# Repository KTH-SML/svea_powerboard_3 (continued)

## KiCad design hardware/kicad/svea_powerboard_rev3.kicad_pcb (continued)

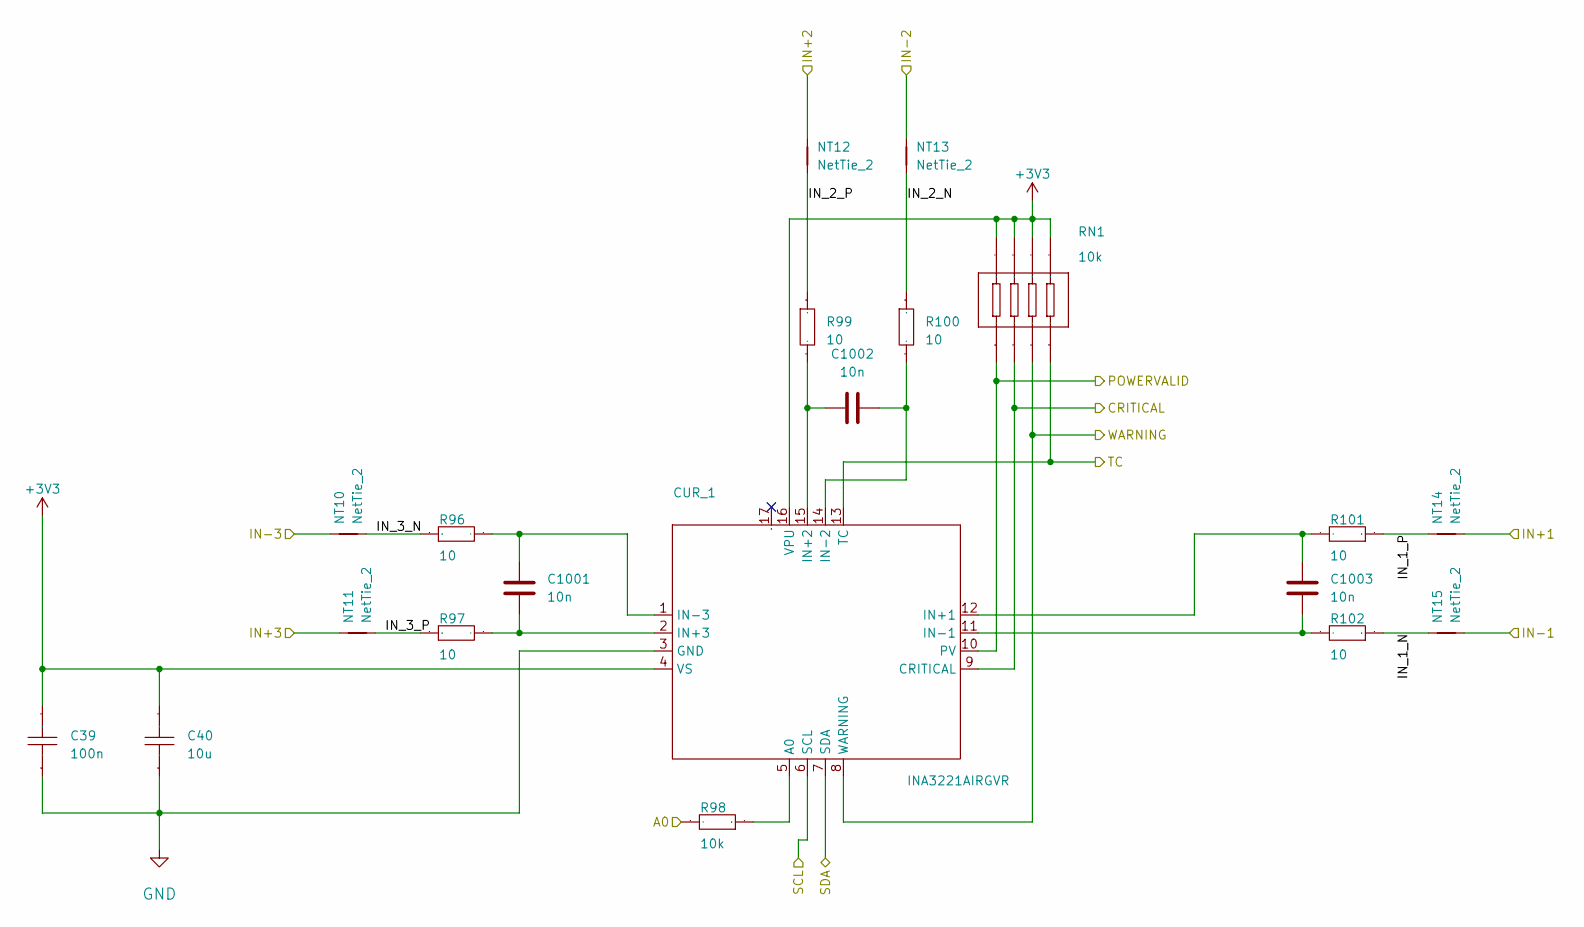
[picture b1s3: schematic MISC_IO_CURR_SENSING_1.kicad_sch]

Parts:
C39: 100n; C_0603_1608Metric; Manufacturer Part CC0603KRX7R9BB104; LCSC Part Name 100nF ±10% 50V
C40: 10u; C_0805_2012Metric; Manufacturer Part GRM21BR61H106KE43L; LCSC Part Name 10uF ±10% 50V
C1001, C1002, C1003: 10n; C_0402_1005Metric; LCSC C15195
CUR_1: INA3221AIRGVR; Texas_RGV0016A_VQFN-16-1EP_4x4mm_P0.65mm_EP2.1x2.1mm; Manufacturer Part INA3221AIRGVR; LCSC Part Name INA3221AIRGVR
NT10, NT11, NT12, NT13, NT14, NT15: NetTie_2; NetTie-2_SMD_Pad0.2mm
R96, R97, R99, R100, R101, R102: 10; R_0402_1005Metric; Manufacturer Part RC0402FR-0710RL; LCSC Part Name 厚膜电阻 10Ω ±1% 62.5mW
R98: 10k; R_0402_1005Metric; Manufacturer Part 0402WGF1002TCE; LCSC Part Name 10kΩ ±1% 62.5mW 厚膜电阻
RN1: 10k; R_Array_Convex_4x0603; Manufacturer Part RTA03-4D103JTP; LCSC Part Name 10kΩ ±5%

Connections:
+3V3: C39.2, C40.2, CUR_1.4 (VS), CUR_1.16 (VPU), RN1.5, RN1.6, RN1.7, RN1.8; also elsewhere on the board
+12V: NT11.2, NT12.2, NT14.1; also elsewhere on the board
/Battery System/CUR1/IN-1: NT15.1; also elsewhere on the board
/Battery System/CUR1/IN-2: NT13.2; also elsewhere on the board
/Battery System/CUR1/IN-3: NT10.2; also elsewhere on the board
/Battery System/CUR1/IN_1_N: NT15.2, R102.1
/Battery System/CUR1/IN_1_P: NT14.2, R101.1
/Battery System/CUR1/IN_2_N: NT13.1, R100.1
/Battery System/CUR1/IN_2_P: NT12.1, R99.1
/Battery System/CUR1/IN_3_N: NT10.1, R96.1
/Battery System/CUR1/IN_3_P: NT11.1, R97.1
Current/INA3221-CUR1/CRITICAL: CUR_1.9 (CRITICAL), RN1.2; also elsewhere on the board
Current/INA3221-CUR1/POWERVALID: CUR_1.10 (PV), RN1.1; also elsewhere on the board
Current/INA3221-CUR1/TC: CUR_1.13 (TC), RN1.4; also elsewhere on the board
Current/INA3221-CUR1/WARNING: CUR_1.8 (WARNING), RN1.3; also elsewhere on the board
GND: C39.1, C40.1, CUR_1.3 (GND), R98.2; also elsewhere on the board
unnamed: CUR_1.5 (A0), R98.1
unnamed: C1003.2, CUR_1.12 (IN+1), R101.2
unnamed: C1002.1, CUR_1.15 (IN+2), R99.2
unnamed: C1001.2, CUR_1.2 (IN+3), R97.2
unnamed: C1003.1, CUR_1.11 (IN-1), R102.2
unnamed: C1002.2, CUR_1.14 (IN-2), R100.2
unnamed: C1001.1, CUR_1.1 (IN-3), R96.2
SCL_SLOW: CUR_1.6 (SCL); also elsewhere on the board
SDA_SLOW: CUR_1.7 (SDA); also elsewhere on the board

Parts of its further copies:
C102: 100n; C_0603_1608Metric; Manufacturer Part CC0603KRX7R9BB104; LCSC Part Name 100nF ±10% 50V
C103: 10u; C_0805_2012Metric; Manufacturer Part GRM21BR61H106KE43L; LCSC Part Name 10uF ±10% 50V
C2801, C2802, C2803: 10n; C_0402_1005Metric; LCSC C15195
CUR_2: INA3221AIRGVR; Texas_RGV0016A_VQFN-16-1EP_4x4mm_P0.65mm_EP2.1x2.1mm; Manufacturer Part INA3221AIRGVR; LCSC Part Name INA3221AIRGVR
NT20, NT21, NT22, NT23, NT24, NT25: NetTie_2; NetTie-2_SMD_Pad0.2mm
R160, R161, R163, R164, R165, R166: 10; R_0402_1005Metric; Manufacturer Part RC0402FR-0710RL; LCSC Part Name 厚膜电阻 10Ω ±1% 62.5mW
R162: 10k; R_0402_1005Metric; Manufacturer Part 0402WGF1002TCE; LCSC Part Name 10kΩ ±1% 62.5mW 厚膜电阻
RN2: 10k; R_Array_Convex_4x0603; Manufacturer Part RTA03-4D103JTP; LCSC Part Name 10kΩ ±5%

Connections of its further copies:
+3V3: C102.2, C103.2, CUR_2.4 (VS), CUR_2.16 (VPU), R162.2, RN2.5, RN2.6, RN2.7, RN2.8; also elsewhere on the board
+12V: NT20.2; also elsewhere on the board
/Battery System/CUR2/IN+3: NT21.2; also elsewhere on the board
/Battery System/CUR2/IN-1: NT25.1; also elsewhere on the board
/Battery System/CUR2/IN-2: NT23.2; also elsewhere on the board
/Battery System/CUR2/IN_1_N: NT25.2, R166.1
/Battery System/CUR2/IN_1_P: NT24.2, R165.1
/Battery System/CUR2/IN_2_N: NT23.1, R164.1
/Battery System/CUR2/IN_2_P: NT22.1, R163.1
/Battery System/CUR2/IN_3_N: NT20.1, R160.1
/Battery System/CUR2/IN_3_P: NT21.1, R161.1
Current/INA3221-CUR2/CRITICAL: CUR_2.9 (CRITICAL), RN2.2; also elsewhere on the board
Current/INA3221-CUR2/POWERVALID: CUR_2.10 (PV), RN2.1; also elsewhere on the board
Current/INA3221-CUR2/TC: CUR_2.13 (TC), RN2.4; also elsewhere on the board
Current/INA3221-CUR2/WARNING: CUR_2.8 (WARNING), RN2.3; also elsewhere on the board
GND: C102.1, C103.1, CUR_2.3 (GND); also elsewhere on the board
unnamed: CUR_2.5 (A0), R162.1
unnamed: C2803.2, CUR_2.12 (IN+1), R165.2
unnamed: C2802.1, CUR_2.15 (IN+2), R163.2
unnamed: C2801.2, CUR_2.2 (IN+3), R161.2
unnamed: C2803.1, CUR_2.11 (IN-1), R166.2
unnamed: C2802.2, CUR_2.14 (IN-2), R164.2
unnamed: C2801.1, CUR_2.1 (IN-3), R160.2
PACK+: NT22.2; also elsewhere on the board
SCL_SLOW: CUR_2.6 (SCL); also elsewhere on the board
SDA_SLOW: CUR_2.7 (SDA); also elsewhere on the board
VCC: NT24.1; also elsewhere on the board

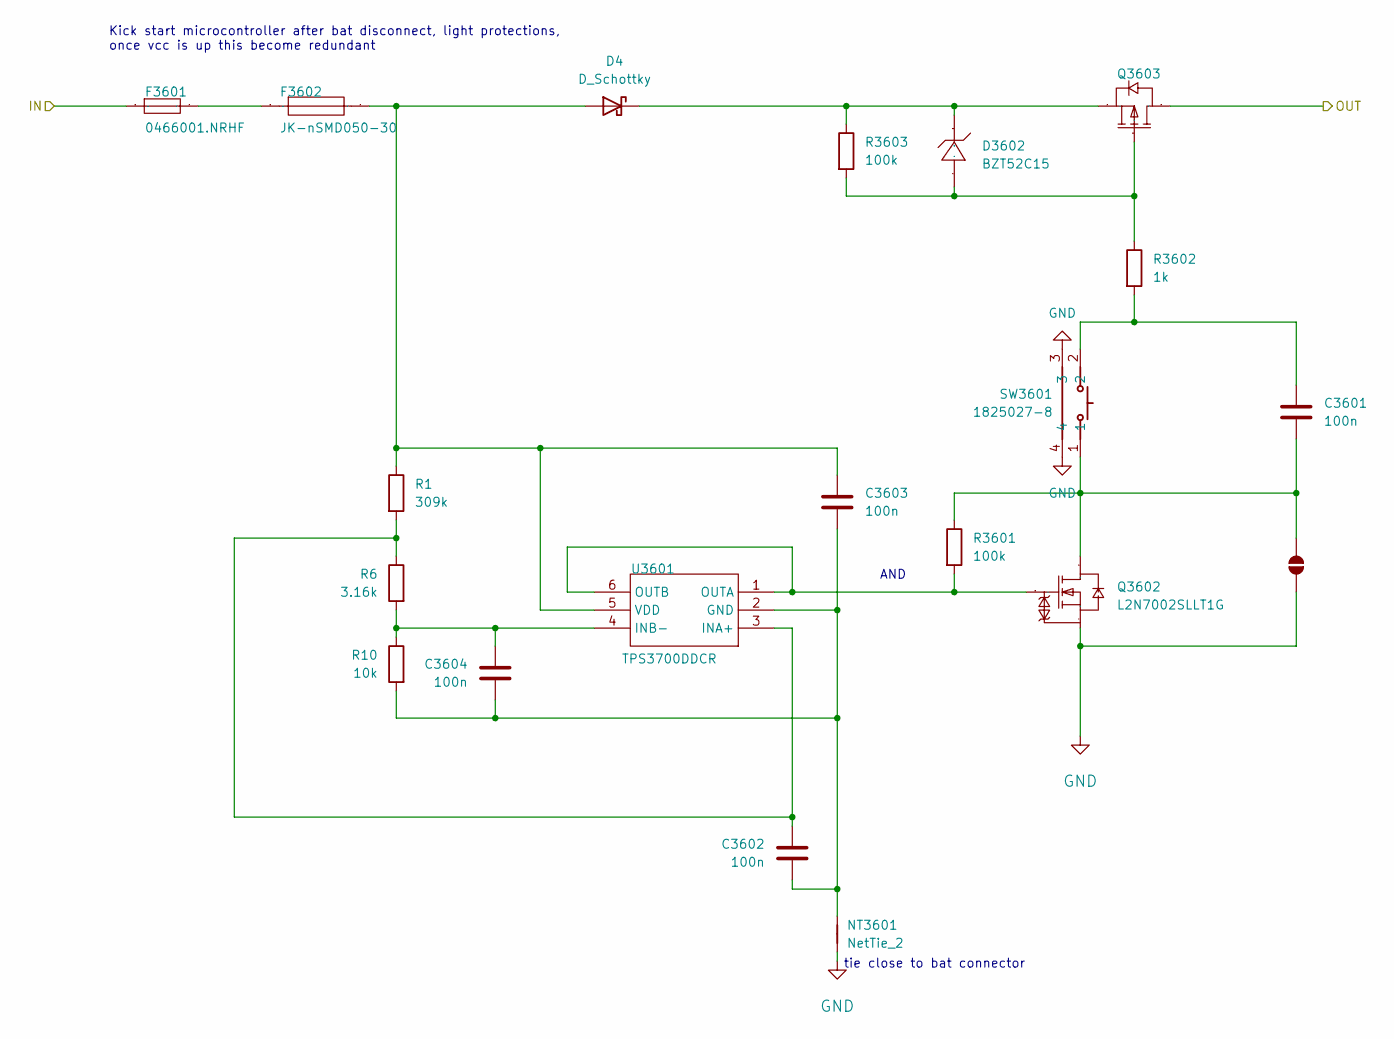
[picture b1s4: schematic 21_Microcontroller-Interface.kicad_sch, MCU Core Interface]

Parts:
C3601, C3602, C3603, C3604: 100n; C_0402_1005Metric; LCSC C307331
D4: D_Schottky; D_SOD-123F; LCSC C719833
D3602: BZT52C15; D_SOD-123; Manufacturer Part BZT52C15; LCSC Part Name BZT52C15
F3601: 0466001.NRHF; Fuse_1206_3216Metric; Manufacturer Part 0466001.NRHF; LCSC Part Name 63V贴片式保险丝
F3602: JK-nSMD050-30; Fuse_1206_3216Metric; Manufacturer Part JK-nSMD050-30; LCSC Part Name 30V 500mA 1206自恢复
JP3601: SolderJumper_2_Open; SolderJumper-2_P1.3mm_Open_TrianglePad1.0x1.5mm
NT3601: NetTie_2; NetTie-2_SMD_Pad0.2mm
Q3602: L2N7002SLLT1G; SOT-23; Manufacturer Part L2N7002SLLT1G; LCSC Part Name 1个N沟道 耐压:60V 电流:380mA
Q3603: SI2309A; SOT-23; Manufacturer Part SI2309A; LCSC Part Name 1个P沟道 耐压:60V 电流:1.25A
R1: 309k; R_0402_1005Metric
R6: 3.16k; R_0402_1005Metric
R10: 10k; R_0402_1005Metric
R3601, R3603: 100k; R_0402_1005Metric; LCSC C25741
R3602: 1k; R_0402_1005Metric; LCSC C11702
SW3601: 1825027-8; Manufacturer Part 1825027-8; LCSC C266196
U3601: TPS3700DDCR; SOT-23-6; Manufacturer Part TPS3700DDCR; LCSC Part Name 用于过压和欠压检测的窗口比较器

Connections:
/Battery System/Battery BMS Interface/BQ-BAT: F3601.1; also elsewhere on the board
/Battery System/danger_rail: Q3603.3 (D); also elsewhere on the board
GND: JP3601.1 (A), NT3601.1, Q3602.2 (S), SW3601.3, SW3601.4; also elsewhere on the board
unnamed: C3601.1, R3602.2, SW3601.2
unnamed: C3603.1, D4.2 (A), F3602.2, R1.1, U3601.5 (VDD)
unnamed: D3602.2 (A), Q3603.1 (G), R3602.1, R3603.2
unnamed: D4.1 (K), D3602.1 (K), Q3603.2 (S), R3603.1
unnamed: F3601.2, F3602.1
unnamed: C3601.2, JP3601.2 (B), Q3602.3 (D), R3601.1, SW3601.1
unnamed: Q3602.1 (G), R3601.2, U3601.1 (OUTA), U3601.6 (OUTB)
unnamed: C3602.2, C3603.2, C3604.2, NT3601.2, R10.2, U3601.2 (GND)
unnamed: C3602.1, R1.2, R6.1, U3601.3 (INA+)
unnamed: C3604.1, R6.2, R10.1, U3601.4 (INB-)

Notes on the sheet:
Kick start microcontroller after bat disconnect, light protections, once vcc is up this become redundant
AND
tie close to bat connector

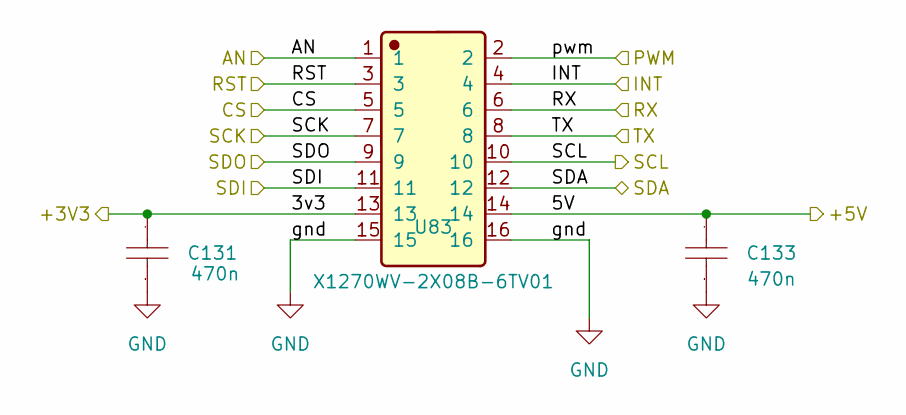
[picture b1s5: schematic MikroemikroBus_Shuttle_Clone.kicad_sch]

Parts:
C131, C133: 470n; C_0603_1608Metric; Manufacturer Part 0603B474K500NT; LCSC Part Name 470nF ±10% 50V
U83: X1270WV-2X08B-6TV01; Manufacturer Part X1270WV-2x08B-9TV01; LCSC C5147219

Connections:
+3V3: C131.2, U83.13; also elsewhere on the board
+5V: C133.2, U83.14; also elsewhere on the board
/Battery System/Mikroe mikroBus Shuttle Clone VITAL/CS: U83.5
/Battery System/Mikroe mikroBus Shuttle Clone VITAL/RST: U83.3
/Battery System/Mikroe mikroBus Shuttle Clone VITAL/SCK: U83.7
/Battery System/Mikroe mikroBus Shuttle Clone VITAL/SDI: U83.11
/Battery System/Mikroe mikroBus Shuttle Clone VITAL/SDO: U83.9
/Battery System/Mikroe mikroBus Shuttle Clone VITAL/TX: U83.8
Button/LOW: U83.1; also elsewhere on the board
GND: C131.1, C133.1, U83.15, U83.16; also elsewhere on the board
IO-Expander/Primary/INT: U83.4; also elsewhere on the board
LED/WS2815/DATA: U83.2; also elsewhere on the board
SBUS_RECEIVER: U83.6; also elsewhere on the board
SCL_SLOW: U83.10; also elsewhere on the board
SDA_SLOW: U83.12; also elsewhere on the board

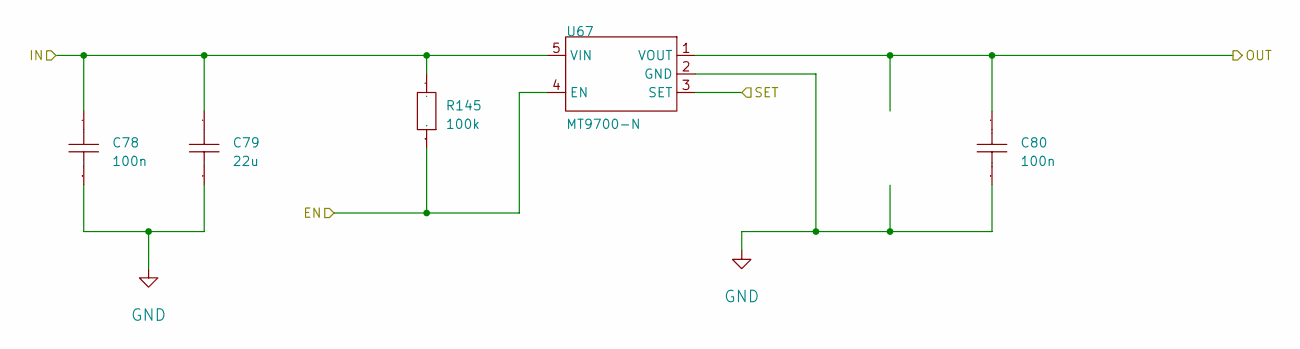
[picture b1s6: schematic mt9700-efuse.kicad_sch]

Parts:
C78, C80: 100n; C_0603_1608Metric; Manufacturer Part CC0603KRX7R9BB104; LCSC Part Name 100nF ±10% 50V
C79: 22u; C_0603_1608Metric; Manufacturer Part CL10A226MP8NUNE; LCSC Part Name 22uF ±20% 10V
R145: 100k; R_0603_1608Metric; Manufacturer Part FRC0603J104 TS; LCSC Part Name 100kΩ ±5% 100mW 厚膜电阻
U67: MT9700-N; SOT-23-5_L2.9-W1.6-P0.95-LS2.9-BL; Manufacturer Part MT9700-N; LCSC Part Name 可调快速响应、限流型电源分配开关

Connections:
+3V3: C78.2, C79.2, R145.2, U67.5 (VIN); also elsewhere on the board
/Battery System/ServoConnectors/3v3: C80.2, U67.1 (VOUT); also elsewhere on the board
/Battery System/mt9700-efuse/SET: U67.3 (SET); also elsewhere on the board
GND: C78.1, C79.1, C80.1, U67.2 (GND); also elsewhere on the board
Receiver/EN: R145.1, U67.4 (EN); also elsewhere on the board

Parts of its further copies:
C107, C109: 100n; C_0603_1608Metric; Manufacturer Part CC0603KRX7R9BB104; LCSC Part Name 100nF ±10% 50V
C108: 22u; C_0603_1608Metric; Manufacturer Part CL10A226MP8NUNE; LCSC Part Name 22uF ±20% 10V
R168: 100k; R_0603_1608Metric; Manufacturer Part FRC0603J104 TS; LCSC Part Name 100kΩ ±5% 100mW 厚膜电阻
U76: MT9700-N; SOT-23-5_L2.9-W1.6-P0.95-LS2.9-BL; Manufacturer Part MT9700-N; LCSC Part Name 可调快速响应、限流型电源分配开关

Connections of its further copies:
+LCL_5V: C109.2, U76.1 (VOUT); also elsewhere on the board
/Battery System/5v rail/5V buck rail: C107.2, C108.2, R168.2, U76.5 (VIN); also elsewhere on the board
/Battery System/mt9700-efuse1/EN: R168.1, U76.4 (EN)
/Battery System/mt9700-efuse1/SET: U76.3 (SET); also elsewhere on the board
GND: C107.1, C108.1, C109.1, U76.2 (GND); also elsewhere on the board

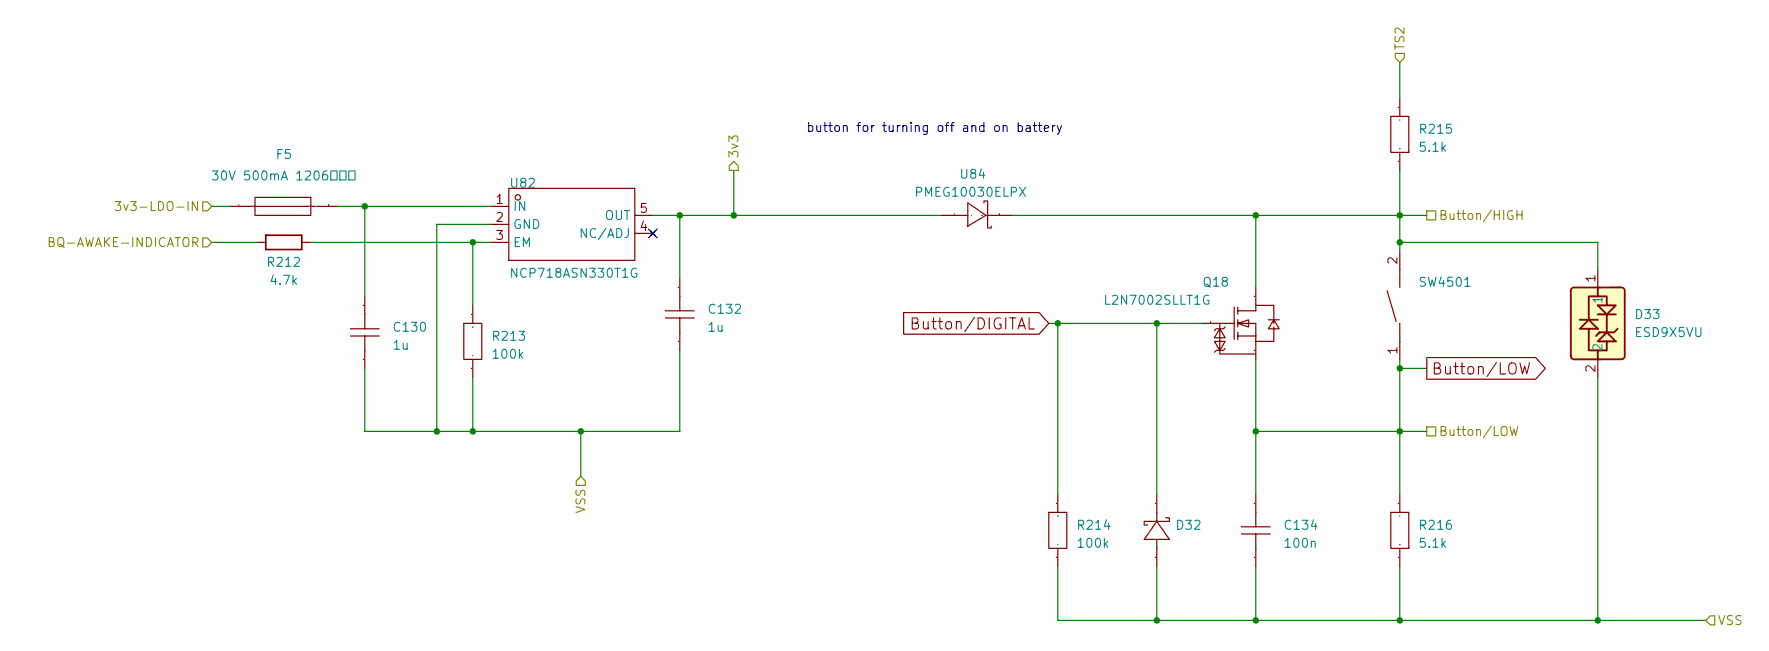
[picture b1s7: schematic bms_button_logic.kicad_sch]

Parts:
C130, C132: 1u; C_0603_1608Metric; Manufacturer Part CL10A105KB8NNNC; LCSC Part Name 1uF ±10% 50V
C134: 100n; C_0603_1608Metric; Manufacturer Part CC0603KRX7R9BB104; LCSC Part Name 100nF ±10% 50V
D32: UCLAMP3301P; DFN1006-2L-RD; Manufacturer Part UCLAMP3301P; LCSC Part Name 单向TVS 3.3V截止 峰值浪涌电流：4A@8/20us
D33: ESD9X5VU; Manufacturer Part ESD9X5VU; LCSC C2875160
F5: JK-nSMD050-30; Fuse_1206_3216Metric; Manufacturer Part JK-nSMD050-30; LCSC Part Name 30V 500mA 1206自恢复
Q18: L2N7002SLLT1G; SOT-23; Manufacturer Part L2N7002SLLT1G; LCSC Part Name 1个N沟道 耐压:60V 电流:380mA
R212: 4.7k; R_0603_1608Metric; LCSC C23162
R213, R214: 100k; R_0603_1608Metric; Manufacturer Part FRC0603J104 TS; LCSC Part Name 100kΩ ±5% 100mW 厚膜电阻
R215, R216: 5.1k; R_0603_1608Metric; Manufacturer Part FRC0603F5101TS; LCSC Part Name 5.1kΩ ±1% 100mW 厚膜电阻
SW4501: TS-1088-AR02016; SW-SMD_L3.9-W3.0-P4.45; Manufacturer Part TS-1088-AR02016; LCSC Part Name 4*3*2mm 立贴 轻触开关
U82: NCP718ASN330T1G; TSOT-23-5; Manufacturer Part NCP718ASN330T1G; LCSC Part Name NCP718ASN330T1G
U84: PMEG10030ELPX; D_SOD-128; Manufacturer Part PMEG10030ELPX; LCSC Part Name 电压:100V 电流:3A

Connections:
/Battery System/Battery BMS Interface/ALERT_PULLUP: C132.2, U82.5 (OUT), U84.2 (A); also elsewhere on the board
/Battery System/Battery BMS Interface/BQ-BAT: F5.2; also elsewhere on the board
/Battery System/Battery BMS Interface/REG18: R212.2; also elsewhere on the board
/Battery System/Battery BMS Interface/TS2: R215.2; also elsewhere on the board
/Battery System/Battery BMS Interface/VSS: C130.1, C132.1, C134.1, D32.2 (A), D33.2, R213.2, R214.2, R216.1, U82.2 (GND); also elsewhere on the board
/Battery System/bms_button_logic/Button/HIGH: D33.1, Q18.3 (D), R215.1, SW4501.2, U84.1 (K)
Button/DIGITAL: D32.1 (K), Q18.1 (G), R214.1; also elsewhere on the board
Button/LOW: C134.2, Q18.2 (S), R216.2, SW4501.1; also elsewhere on the board
unnamed: R212.1, R213.1, U82.3 (EM)
unnamed: C130.2, F5.1, U82.1 (IN)

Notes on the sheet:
button for turning off and on battery

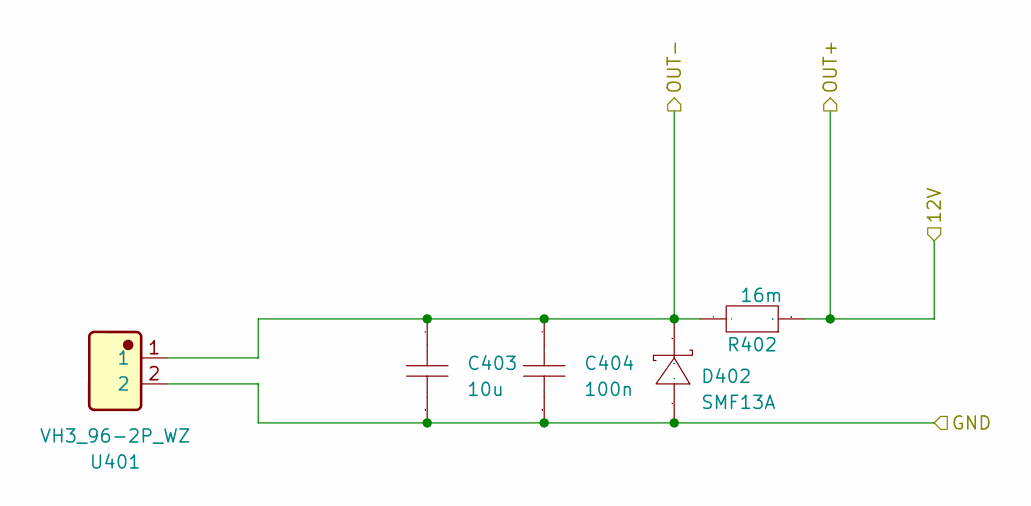
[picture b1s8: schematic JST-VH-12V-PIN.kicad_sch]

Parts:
C403: 10u; C_0805_2012Metric; Manufacturer Part GRM21BR61H106KE43L; LCSC Part Name 10uF ±10% 50V
C404: 100n; C_0603_1608Metric; Manufacturer Part CC0603KRX7R9BB104; LCSC Part Name 100nF ±10% 50V
D402: SMF13A; SOD-123FL_L2.8-W1.8-LS3.6-RD; Manufacturer Part SMF13A; LCSC Part Name SMF13A
R402: 16m; R_2512_6332Metric; Manufacturer Part LR123WF160MT4E; LCSC Part Name 16mΩ ±1% 3W
U401: VH3_96-2P_WZ; Manufacturer Part VH3.96-2P WZ; LCSC C5379879

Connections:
+12V: R402.1; also elsewhere on the board
/Battery System/CUR1/IN-3: C403.2, C404.2, D402.1 (K), R402.2, U401.1; also elsewhere on the board
GND: C403.1, C404.1, D402.2 (A), U401.2; also elsewhere on the board

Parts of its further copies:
C46, C501: 10u; C_0805_2012Metric; Manufacturer Part GRM21BR61H106KE43L; LCSC Part Name 10uF ±10% 50V
C47, C502: 100n; C_0603_1608Metric; Manufacturer Part CC0603KRX7R9BB104; LCSC Part Name 100nF ±10% 50V
D14, D501: SMF13A; SOD-123FL_L2.8-W1.8-LS3.6-RD; Manufacturer Part SMF13A; LCSC Part Name SMF13A
R104, R501: 16m; R_2512_6332Metric; Manufacturer Part LR123WF160MT4E; LCSC Part Name 16mΩ ±1% 3W
U42, U501: VH3_96-2P_WZ; Manufacturer Part VH3.96-2P WZ; LCSC C5379879

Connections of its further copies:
+12V: R104.1, R501.1; also elsewhere on the board
/Battery System/CUR1/IN-1: C501.2, C502.2, D501.1 (K), R501.2, U501.1; also elsewhere on the board
/Battery System/CUR1/IN-2: C46.2, C47.2, D14.1 (K), R104.2, U42.1; also elsewhere on the board
GND: C46.1, C47.1, C501.1, C502.1, D14.2 (A), D501.2 (A), U42.2, U501.2; also elsewhere on the board

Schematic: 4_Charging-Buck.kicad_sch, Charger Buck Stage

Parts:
C20, C21: 22u; C_1210_3225Metric; LCSC C778721
C23: 100n; C_0603_1608Metric; Manufacturer Part CC0603KRX7R9BB104; LCSC Part Name 100nF ±10% 50V
C32: RVT1H220M0605; Manufacturer Part RVT1H220M0605; LCSC C72505
C601: 10u; C_1206_3216Metric; LCSC C89632
C602: UWT1H221MNL1GS; Manufacturer Part UWT1H221MNL1GS; LCSC C125977
C603: 470p; C_0402_1005Metric; LCSC C1537
C604: 220n; C_0402_1005Metric; LCSC C694490
C605, C606, C608: 100n; C_0402_1005Metric; LCSC C307331
C607: 2p; C_0402_1005Metric; LCSC C1558
D11, D12: SBR8U60P5-13; POWERDI-5_L5.4-W4.0-LS6.5-RD; Manufacturer Part SBR8U60P5-13; LCSC Part Name 60V 8A
D601: BZT52C3V3-E3-18; D_SOD-123F; LCSC C5224067
L602: DEP1016NP-220PB; Manufacturer Part DEP1016NP-220PB; LCSC C2897825
LED6: PSC-1608U50GC-G4; LED_0603_1608Metric; Manufacturer Part PSC-1608U50GC-G4; LCSC Part Name 钻孔1608高亮绿灯
LED7: 19-217UYOC/S3112/TR8; LED_0603_1608Metric; Manufacturer Part 19-217UYOC/S3112/TR8; LCSC Part Name 琥珀
NT602: NetTie_2; NetTie-2_SMD_Pad0.3mm
Q1: L2N7002SLLT1G; Manufacturer Part L2N7002SLLT1G; LCSC C22446827
Q601: L2N7002SLLT1G; SOT-23; Manufacturer Part L2N7002SLLT1G; LCSC C22446827
Q602: AO4459; Manufacturer Part AO4459; LCSC C49047
R74, R603, R609: 10k; R_0402_1005Metric; LCSC C25744
R77, R79: 1k; R_0603_1608Metric; Manufacturer Part 0402WGF1001TCE; LCSC Part Name 1kΩ ±1% 62.5mW 厚膜电阻
R86: 60m; R_2512_6332Metric; Manufacturer Part PE2512FKE7W0R06L; LCSC Part Name 薄膜电阻 60mΩ ±1% 2W
R87: --; R_2512_6332Metric; Manufacturer Part PE2512FKE7W0R06L; LCSC Part Name 薄膜电阻 60mΩ ±1% 2W; not fitted
R601: 1M; R_0402_1005Metric; LCSC C26083
R602: 120; R_0402_1005Metric; LCSC C25079
R604, R606, R610: 100k; R_0402_1005Metric; LCSC C25741
R605: 5.76k; R_0402_1005Metric; LCSC C5153969
R607: 105k; R_0402_1005Metric; LCSC C2933067
R608: 24.9k; R_0402_1005Metric; LCSC C138027
U30: CN3722; TSSOP-16_4.4x5mm_P0.65mm; Manufacturer Part CN3722; LCSC Part Name CN3722
U601: TI TPL0401B-10DCKR; Texas_R-PDSO-G6; lcsc C2666599

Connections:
+3V3: R74.1, R77.2, R79.2, R609.1, U601.1 (VDD); also elsewhere on the board
CHARGE_DIRECT: C32.1, C601.1, C607.1, NT602.2, R86.2, R87.2, R607.1; also elsewhere on the board
CHARGING-IC/OPEN-DRAIN-DIGIPOT-#EN: D601.1 (K), Q601.1 (G), R610.2; also elsewhere on the board
Charger/CN3072/CHG-ACTIVE: LED7.1 (-), R609.2, U30.4 (CHRG#); also elsewhere on the board
Charger/CN3072/CHG-DONE: LED6.1 (K), R74.2, U30.5 (DONE#); also elsewhere on the board
Charger/CN3722/EN#: Q1.1 (G), R604.1; also elsewhere on the board
GND: C20.1, C21.1, C23.1, C32.2, C601.2, C602.2, C603.2, C604.2, C605.2, C608.2, D12.1, D12.2, D601.2 (A), Q1.2 (S), Q601.2 (S), R601.2, R603.2, R604.2, R608.2, U30.2 (PGND), U30.3 (GND), U601.2 (GND); also elsewhere on the board
IN-CHARGING-VCC-LIMITED: C20.2, C21.2, C23.2, C602.1, C606.1, C608.1, Q602.1 (S), Q602.2 (S), Q602.3 (S), R606.1, R610.1, U30.15 (VCC); also elsewhere on the board
unnamed: C604.1, R602.2
unnamed: D11.1, D11.2, Q602.5 (D), Q602.6 (D), Q602.7 (D), Q602.8 (D)
unnamed: D11.3, D12.3, L602.2
unnamed: LED6.2 (A), R77.1
unnamed: LED7.2 (+), R79.1
unnamed: Q1.3 (D), R603.1, U30.6 (TEMP)
unnamed: Q601.3 (D), R605.2, U601.5 (W), U601.6 (H)
unnamed: Q602.4 (G), U30.16 (DRV)
unnamed: NT602.1, U30.14 (BAT)
unnamed: C603.1, R601.1, U30.8 (COM1)
unnamed: R602.1, U30.9 (COM2)
unnamed: C605.1, U30.11 (COM3)
unnamed: L602.1, R86.1, R87.1, U30.13 (CSP)
unnamed: C607.2, R607.2, R608.1, U30.10 (FB)
unnamed: R605.1, R606.2, U30.7 (MPPT)
unnamed: C606.2, U30.1 (VG)
SCL_SLOW: U601.3 (SCL); also elsewhere on the board
SDA_SLOW: U601.4 (SDA); also elsewhere on the board

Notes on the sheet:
typ 19.1V
Default 3A, solder another in parallel for higher current
metal resistor to lead heat away

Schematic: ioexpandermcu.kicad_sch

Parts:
C142: 100n; C_0603_1608Metric; Manufacturer Part CC0603KRX7R9BB104; LCSC Part Name 100nF ±10% 50V
R268, R269: 10k; R_0402_1005Metric; Manufacturer Part 0402WGF1002TCE; LCSC Part Name 10kΩ ±1% 62.5mW 厚膜电阻
U301, U302, U303: EXB2HV102JV; R_Array_Convex_8x0602; Manufacturer Part EXB2HV102JV; LCSC C713453
U304: PCAL6524HEAZ; LFCSP-32-1EP_5x5mm_P0.5mm_EP3.6x3.6mm; Manufacturer Part PCAL6524HEAZ; LCSC C3000497

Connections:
+3V3: C142.2, R268.2, R269.2, U304.27 (VDD(P)), U304.31 (VDD(I2C-bus)); also elsewhere on the board
/Battery System/IO-ExpanderSecondary/ADDR: U304.26 (ADDR); also elsewhere on the board
/Battery System/IO-ExpanderSecondary/P1_2: U302.3
/Battery System/IO-ExpanderSecondary/P1_3: U302.4
/Battery System/IO-ExpanderSecondary/P1_4: U302.5
/Battery System/IO-ExpanderSecondary/P1_7: U302.8
/Battery System/IO-ExpanderSecondary/P2_1: U303.10
/Battery System/IO-ExpanderSecondary/P2_2: U303.11
/Battery System/IO-ExpanderSecondary/P2_4: U303.13
/Battery System/IO-ExpanderSecondary/P2_5: U303.14
Charger/CN3072/CHG-ACTIVE: U302.7; also elsewhere on the board
Charger/CN3072/CHG-DONE: U302.6; also elsewhere on the board
Current/INA226-ESC-0x4E/ALERT: U302.1; also elsewhere on the board
Current/INA226-SERVO-0x4F/ALERT: U302.2; also elsewhere on the board
Current/INA3221-CUR1/CRITICAL: U301.1; also elsewhere on the board
Current/INA3221-CUR1/POWERVALID: U301.3; also elsewhere on the board
Current/INA3221-CUR1/TC: U301.4; also elsewhere on the board
Current/INA3221-CUR1/WARNING: U301.2; also elsewhere on the board
Current/INA3221-CUR2/CRITICAL: U301.5; also elsewhere on the board
Current/INA3221-CUR2/POWERVALID: U301.7; also elsewhere on the board
Current/INA3221-CUR2/TC: U301.8; also elsewhere on the board
Current/INA3221-CUR2/WARNING: U301.6; also elsewhere on the board
GND: C142.1, U304.25 (VSS), U304.33 (EP); also elsewhere on the board
IMU/INT1: U303.16; also elsewhere on the board
IMU/INT2: U303.15; also elsewhere on the board
IO-Expander/Secondary/INT: R268.1, U304.32 (INT#); also elsewhere on the board
unnamed: U301.16, U304.1 (P0_0)
unnamed: U301.15, U304.2 (P0_1)
unnamed: U301.14, U304.3 (P0_2)
unnamed: U301.13, U304.4 (P0_3)
unnamed: U301.12, U304.5 (P0_4)
unnamed: U301.11, U304.6 (P0_5)
unnamed: U301.10, U304.7 (P0_6)
unnamed: U301.9, U304.8 (P0_7)
unnamed: U302.16, U304.9 (P1_0)
unnamed: U302.15, U304.10 (P1_1)
unnamed: U302.14, U304.11 (P1_2)
unnamed: U302.13, U304.12 (P1_3)
unnamed: U302.12, U304.13 (P1_4)
unnamed: U302.11, U304.14 (P1_5)
unnamed: U302.10, U304.15 (P1_6)
unnamed: U302.9, U304.16 (P1_7)
unnamed: U303.8, U304.17 (P2_0)
unnamed: U303.7, U304.18 (P2_1)
unnamed: U303.6, U304.19 (P2_2)
unnamed: U303.5, U304.20 (P2_3)
unnamed: U303.4, U304.21 (P2_4)
unnamed: U303.3, U304.22 (P2_5)
unnamed: U303.2, U304.23 (P2_6)
unnamed: U303.1, U304.24 (P2_7)
unnamed: R269.1, U304.28 (RESET#)
SCL_SLOW: U304.29 (SCL); also elsewhere on the board
SDA_SLOW: U304.30 (SDA); also elsewhere on the board
USB-C/HUSB238A/FAULT-OUT2: U303.9; also elsewhere on the board
USB-C/HUSB238A/INT: U303.12; also elsewhere on the board

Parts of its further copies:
C141: 100n; C_0603_1608Metric; Manufacturer Part CC0603KRX7R9BB104; LCSC Part Name 100nF ±10% 50V
R241, R242: 10k; R_0402_1005Metric; Manufacturer Part 0402WGF1002TCE; LCSC Part Name 10kΩ ±1% 62.5mW 厚膜电阻
U3401, U3402, U3403: EXB2HV102JV; R_Array_Convex_8x0602; Manufacturer Part EXB2HV102JV; LCSC C713453
U3404: PCAL6524HEAZ; LFCSP-32-1EP_5x5mm_P0.5mm_EP3.6x3.6mm; Manufacturer Part PCAL6524HEAZ; LCSC C3000497

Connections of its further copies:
+3V3: C141.2, R241.2, R242.2, U3404.27 (VDD(P)), U3404.31 (VDD(I2C-bus)); also elsewhere on the board
/Battery System/IO-ExpanderPrimary/ADDR: U3404.26 (ADDR); also elsewhere on the board
/Battery System/IO-ExpanderPrimary/P0_3: U3401.4
/Battery System/IO-ExpanderPrimary/P1_4: U3402.5
/Battery System/IO-ExpanderPrimary/P1_7: U3402.8
/Battery System/IO-ExpanderPrimary/P2_2: U3403.11
/Battery System/IO-ExpanderPrimary/P2_4: U3403.13
ADS1115/ALERT: U3403.12; also elsewhere on the board
BQ/ALERT/LED: U3401.1; also elsewhere on the board
BQ/RST-SHUT: U3401.2; also elsewhere on the board
Button/DIGITAL: U3401.6; also elsewhere on the board
Button/LOW: U3403.14; also elsewhere on the board
CHARGING-IC/OPEN-DRAIN-DIGIPOT-#EN: U3401.7; also elsewhere on the board
Charger/CN3722/EN#: U3402.7; also elsewhere on the board
ESC/EN: U3402.2; also elsewhere on the board
GND: C141.1, U3404.25 (VSS), U3404.33 (EP); also elsewhere on the board
IO-Expander/Primary/INT: R241.1, U3404.32 (INT#); also elsewhere on the board
IO-Expander/Secondary/INT: U3402.1; also elsewhere on the board
unnamed: U3401.16, U3404.1 (P0_0)
unnamed: U3401.15, U3404.2 (P0_1)
unnamed: U3401.14, U3404.3 (P0_2)
unnamed: U3401.13, U3404.4 (P0_3)
unnamed: U3401.12, U3404.5 (P0_4)
unnamed: U3401.11, U3404.6 (P0_5)
unnamed: U3401.10, U3404.7 (P0_6)
unnamed: U3401.9, U3404.8 (P0_7)
unnamed: U3402.16, U3404.9 (P1_0)
unnamed: U3402.15, U3404.10 (P1_1)
unnamed: U3402.14, U3404.11 (P1_2)
unnamed: U3402.13, U3404.12 (P1_3)
unnamed: U3402.12, U3404.13 (P1_4)
unnamed: U3402.11, U3404.14 (P1_5)
unnamed: U3402.10, U3404.15 (P1_6)
unnamed: U3402.9, U3404.16 (P1_7)
unnamed: U3403.8, U3404.17 (P2_0)
unnamed: U3403.7, U3404.18 (P2_1)
unnamed: U3403.6, U3404.19 (P2_2)
unnamed: U3403.5, U3404.20 (P2_3)
unnamed: U3403.4, U3404.21 (P2_4)
unnamed: U3403.3, U3404.22 (P2_5)
unnamed: U3403.2, U3404.23 (P2_6)
unnamed: U3403.1, U3404.24 (P2_7)
unnamed: R242.1, U3404.28 (RESET#)
Power/5V-Buck/EN#: U3401.8; also elsewhere on the board
Power/5V-Buck/PGOOD: U3401.5; also elsewhere on the board
Power/12V-Buck/EN: U3402.6; also elsewhere on the board
Receiver/EN: U3403.10; also elsewhere on the board
SCL_SLOW: U3404.29 (SCL); also elsewhere on the board
SDA_SLOW: U3404.30 (SDA); also elsewhere on the board
Servo/TPS/EN: U3402.3; also elsewhere on the board
Servo/TPS/PGOOD: U3402.4; also elsewhere on the board
USB-C/HUSB238A/EN#: U3401.3; also elsewhere on the board
eFuse/TPS16630/FAULT: U3403.16; also elsewhere on the board
eFuse/TPS16630/PGOOD: U3403.9; also elsewhere on the board
eFuse/TPS16630/SHDN: U3403.15; also elsewhere on the board

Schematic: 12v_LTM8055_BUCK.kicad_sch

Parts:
C1401, C1403: CL32B475KBUYNNE; C_1210_3225Metric; Manufacturer Part CL32B475KBUYNNE; LCSC C170099
C1402: UUD1H221MNL1GS; Manufacturer Part UUD1H221MNL1GS; LCSC C125976
C1404: 220n; C_0402_1005Metric; LCSC C694490
C1405, C1406: 100n; C_0402_1005Metric; LCSC C307331
C1407: 1u; C_0603_1608Metric; LCSC C5199872
C1408: TPSC686M016R0200; CP_EIA-6032-28_Kemet-C; Manufacturer Part TPSC686M016R0200; LCSC C444808
C1409: CL21A226MAYNNNE; C_0805_2012Metric; Manufacturer Part CL21A226MAYNNNE; LCSC C602037
JP1402: SolderJumper_2_Open; SolderJumper-2_P1.3mm_Open_TrianglePad1.0x1.5mm
JP1403: SolderJumper_2_Bridged; SolderJumper-2_P1.3mm_Bridged_Pad1.0x1.5mm
NT16: NetTie_2; NetTie-2_SMD_Pad0.2mm
NT1401: NetTie_2; NetTie-2_SMD_Pad0.3mm
R112, R1404: 7m; R_2512_6332Metric; Manufacturer Part JER2512F3R007; LCSC Part Name 7mΩ 3W 2512 ±1%
R1401, R1402: 100k; R_0402_1005Metric; LCSC C25741
R1403: 11k; R_0402_1005Metric; LCSC C2909313
R1405: 36.5k; R_0402_1005Metric; LCSC C25887
U44: MCP4725A0T-E/CH; SOT-23-6_L2.9-W1.6-P0.95-LS2.8-BL; Manufacturer Part MCP4725A0T-E/CH; LCSC Part Name MCP4725A0T-E/CH
U47: LTM8055IY_PBF; BGA121C127P11X11_1500X1500X512N; PARTREV Rev C; LCSC Part Name 36VIN、8.5A 降压-升压型 uModule 稳压器

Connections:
+3V3: C1406.1, C1407.1, U44.3 (VDD); also elsewhere on the board
/Battery System/12v_LTM8055_BUCK/12vbuckvintochip: C1401.2, C1402.1, C1403.2, JP1403.2 (B), R1404.2, U47.F10 (SVIN), U47.F11 (SVIN), U47.G10 (VIN), U47.G11 (VIN), U47.H10 (VIN), U47.H11 (VIN), U47.J10 (VIN), U47.J11 (VIN), U47.K10 (VIN), U47.K11 (VIN), U47.L10 (VIN), U47.L11 (VIN)
/Battery System/12v_buck_out_net: NT16.2, R112.2; also elsewhere on the board
GND: C1401.1, C1402.2, C1403.1, C1404.2, C1405.2, C1406.2, C1407.2, C1408.2, C1409.1, R1401.2, R1403.2, R1405.2, U44.2 (VSS), U44.6 (A0), U47.A7 (GND), U47.A8 (GND), U47.A9 (GND), U47.A10 (GND), U47.A11 (GND), U47.B7 (GND), U47.B8 (GND), U47.B9 (GND), U47.B10 (GND), U47.B11 (GND), U47.C7 (GND), U47.C8 (GND), U47.C9 (GND), U47.C10 (GND), U47.C11 (GND), U47.D2 (GND), U47.D3 (GND), U47.D4 (GND), U47.D5 (GND), U47.D6 (GND), U47.D7 (GND), U47.D8 (GND), U47.D9 (GND), U47.D10 (GND), U47.D11 (GND), U47.E1 (GND), U47.E2 (GND), U47.E3 (GND), U47.E4 (GND), U47.E5 (GND), U47.E6 (GND), U47.E7 (GND), U47.E8 (GND), U47.E9 (GND), U47.E10 (GND), U47.E11 (GND), U47.F2 (GND), U47.F3 (GND), U47.F4 (GND), U47.F5 (GND), U47.F6 (GND), U47.F7 (GND), U47.F8 (GND), U47.F9 (GND), U47.G3 (GND), U47.G4 (GND), U47.G5 (GND), U47.G6 (GND), U47.G7 (GND), U47.G8 (GND), U47.G9 (GND), U47.H2 (SYNC), U47.H3 (GND), U47.H4 (GND), U47.H5 (GND), U47.H6 (GND), U47.H7 (GND), U47.H8 (GND), U47.H9 (GND), U47.J3 (GND), U47.J4 (GND), U47.J5 (GND), U47.J6 (GND), U47.J7 (GND), U47.J8 (GND), U47.J9 (GND), U47.K3 (GND), U47.K4 (GND), U47.K5 (GND), U47.K6 (GND), U47.K7 (GND), U47.K8 (GND), U47.K9 (GND), U47.L1 (GND), U47.L5 (GND), U47.L6 (GND), U47.L7 (GND), U47.L8 (GND); also elsewhere on the board
unnamed: C1408.1, C1409.2, R112.1, R1402.1, U47.A1 (VOUT), U47.A2 (VOUT), U47.A3 (VOUT), U47.A4 (VOUT), U47.A5 (VOUT), U47.A6 (VOUT), U47.B1 (VOUT), U47.B2 (VOUT), U47.B3 (VOUT), U47.B4 (VOUT), U47.B5 (VOUT), U47.B6 (VOUT), U47.C1 (VOUT), U47.C2 (VOUT), U47.C3 (VOUT), U47.C4 (VOUT), U47.C5 (VOUT), U47.C6 (VOUT)
unnamed: JP1402.1 (A), U44.1 (VOUT)
unnamed: JP1402.2 (B), U47.K2 (CTL)
unnamed: JP1403.1 (A), NT1401.2, U47.L9 (IIN)
unnamed: R1402.2, R1403.1, U47.J1 (FB)
unnamed: NT16.1, U47.D1 (IOUT)
unnamed: C1405.1, U47.F1 (LL), U47.G2 (MODE)
unnamed: R1405.1, U47.H1 (RT)
unnamed: C1404.1, U47.K1 (SS)
Power/12V-Buck/EN: R1401.1, U47.L4 (RUN); also elsewhere on the board
SCL_SLOW: U44.5 (SCL); also elsewhere on the board
SDA_SLOW: U44.4 (SDA); also elsewhere on the board
VCC: NT1401.1, R1404.1; also elsewhere on the board

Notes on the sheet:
Reverse current protection, when current is less than 0.83A mode is switched to prevent reverse current
8.3A
7.5ms
7.1A
0x60

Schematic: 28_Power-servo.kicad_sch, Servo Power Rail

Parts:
C65, C66: 10u; C_1210_3225Metric; Manufacturer Part GCM32EC71H106KA03L; LCSC Part Name 10uF ±10% 50V
C68: 100u; CAP-SMD_BD5.0-L5.3-W5.3-LS6.3-FD; Manufacturer Part RVT1A101M0505; LCSC Part Name 100uF ±20% 10V
C1701: 100n; C_0603_1608Metric; LCSC C14663
C1702, C1703, C1704: GRM32ER71A476ME15L; C_1210_3225Metric; Manufacturer Part GRM32ER71A476ME15L; LCSC C415541
JP1701, JP1702: SolderJumper_2_Bridged; SolderJumper-2_P1.3mm_Bridged_Pad1.0x1.5mm
NT1702: NetTie_2; NetTie-2_SMD_Pad0.2mm
R121: 100; R_0603_1608Metric; Manufacturer Part FRC0603J101 TS; LCSC Part Name 100Ω ±5% 100mW 厚膜电阻; not fitted
R1701: 47k; R_0402_1005Metric; LCSC C25792
R1702, R1705: 100k; R_0402_1005Metric; LCSC C25741
R1703: 26.7k; R_0402_1005Metric; LCSC C5121521
R1704: 20k; R_0402_1005Metric; LCSC C25765
U55: TPSM63610RDFR; Manufacturer Part TPSM63610RDFR; LCSC C7125816

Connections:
+3V3: R1701.1; also elsewhere on the board
/Battery System/Ideal_Diode_OR_SERVO/IN: C68.1, C1701.2, C1702.2, C1703.2, C1704.2, R1705.1, U55.5 (VLDOIN), U55.9 (VOUT1), U55.10 (VOUT2); also elsewhere on the board
GND: C65.1, C66.2, C68.2, C1701.1, C1702.1, C1703.1, C1704.1, JP1702.1 (A), NT1702.1, R1702.2, R1703.2, R1704.2, U55.7 (AGND), U55.11 (AGND), U55.19 (PGND), U55.20 (PGND), U55.21 (AGND), U55.22 (AGND); also elsewhere on the board
unnamed: JP1701.1 (A), R121.2, U55.2 (RBOOT)
unnamed: JP1701.2 (B), R121.1, U55.3 (CBOOT)
unnamed: JP1702.2 (B), U55.14 (SPSP)
unnamed: R1704.1, R1705.2, U55.8 (FB)
unnamed: NT1702.2, U55.15 (MODE)
unnamed: R1703.1, U55.12 (RT)
PACK+: C65.2, C66.1, U55.1 (VIN1), U55.18 (VIN2); also elsewhere on the board
Servo/TPS/EN: R1702.1, U55.17 (EN); also elsewhere on the board
Servo/TPS/PGOOD: R1701.2, U55.13 (PG); also elsewhere on the board

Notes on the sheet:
highest efficiency, bad emi default cut trace an place 100 ohm for better balance
about 600kHz
MAX 6V
